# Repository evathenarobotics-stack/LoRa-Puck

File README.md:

So this week was a free design, But I was a little busy so I decided to follow the guide of the LoRa Puck.(though I wished I did the keyboard)
So I just followed the guide for the most part, But I did have some issues finding the symbols in the schematic.
When that issue occured, I just created my own by following a guide online and it seems to have worked quite well.

The main purpose of the lora (LOng RAnge) puck is to wirelessly communicate information through radio waves. This is why the schematic has the AE1 Antenna.
Without the use of wifi, celluar, and bluetooth, the lora puck is able to transfer information, such as temperature, motion, and more.
It uses a long lasting battery which makes it more reliable in situations where wifi isn't avaliable.

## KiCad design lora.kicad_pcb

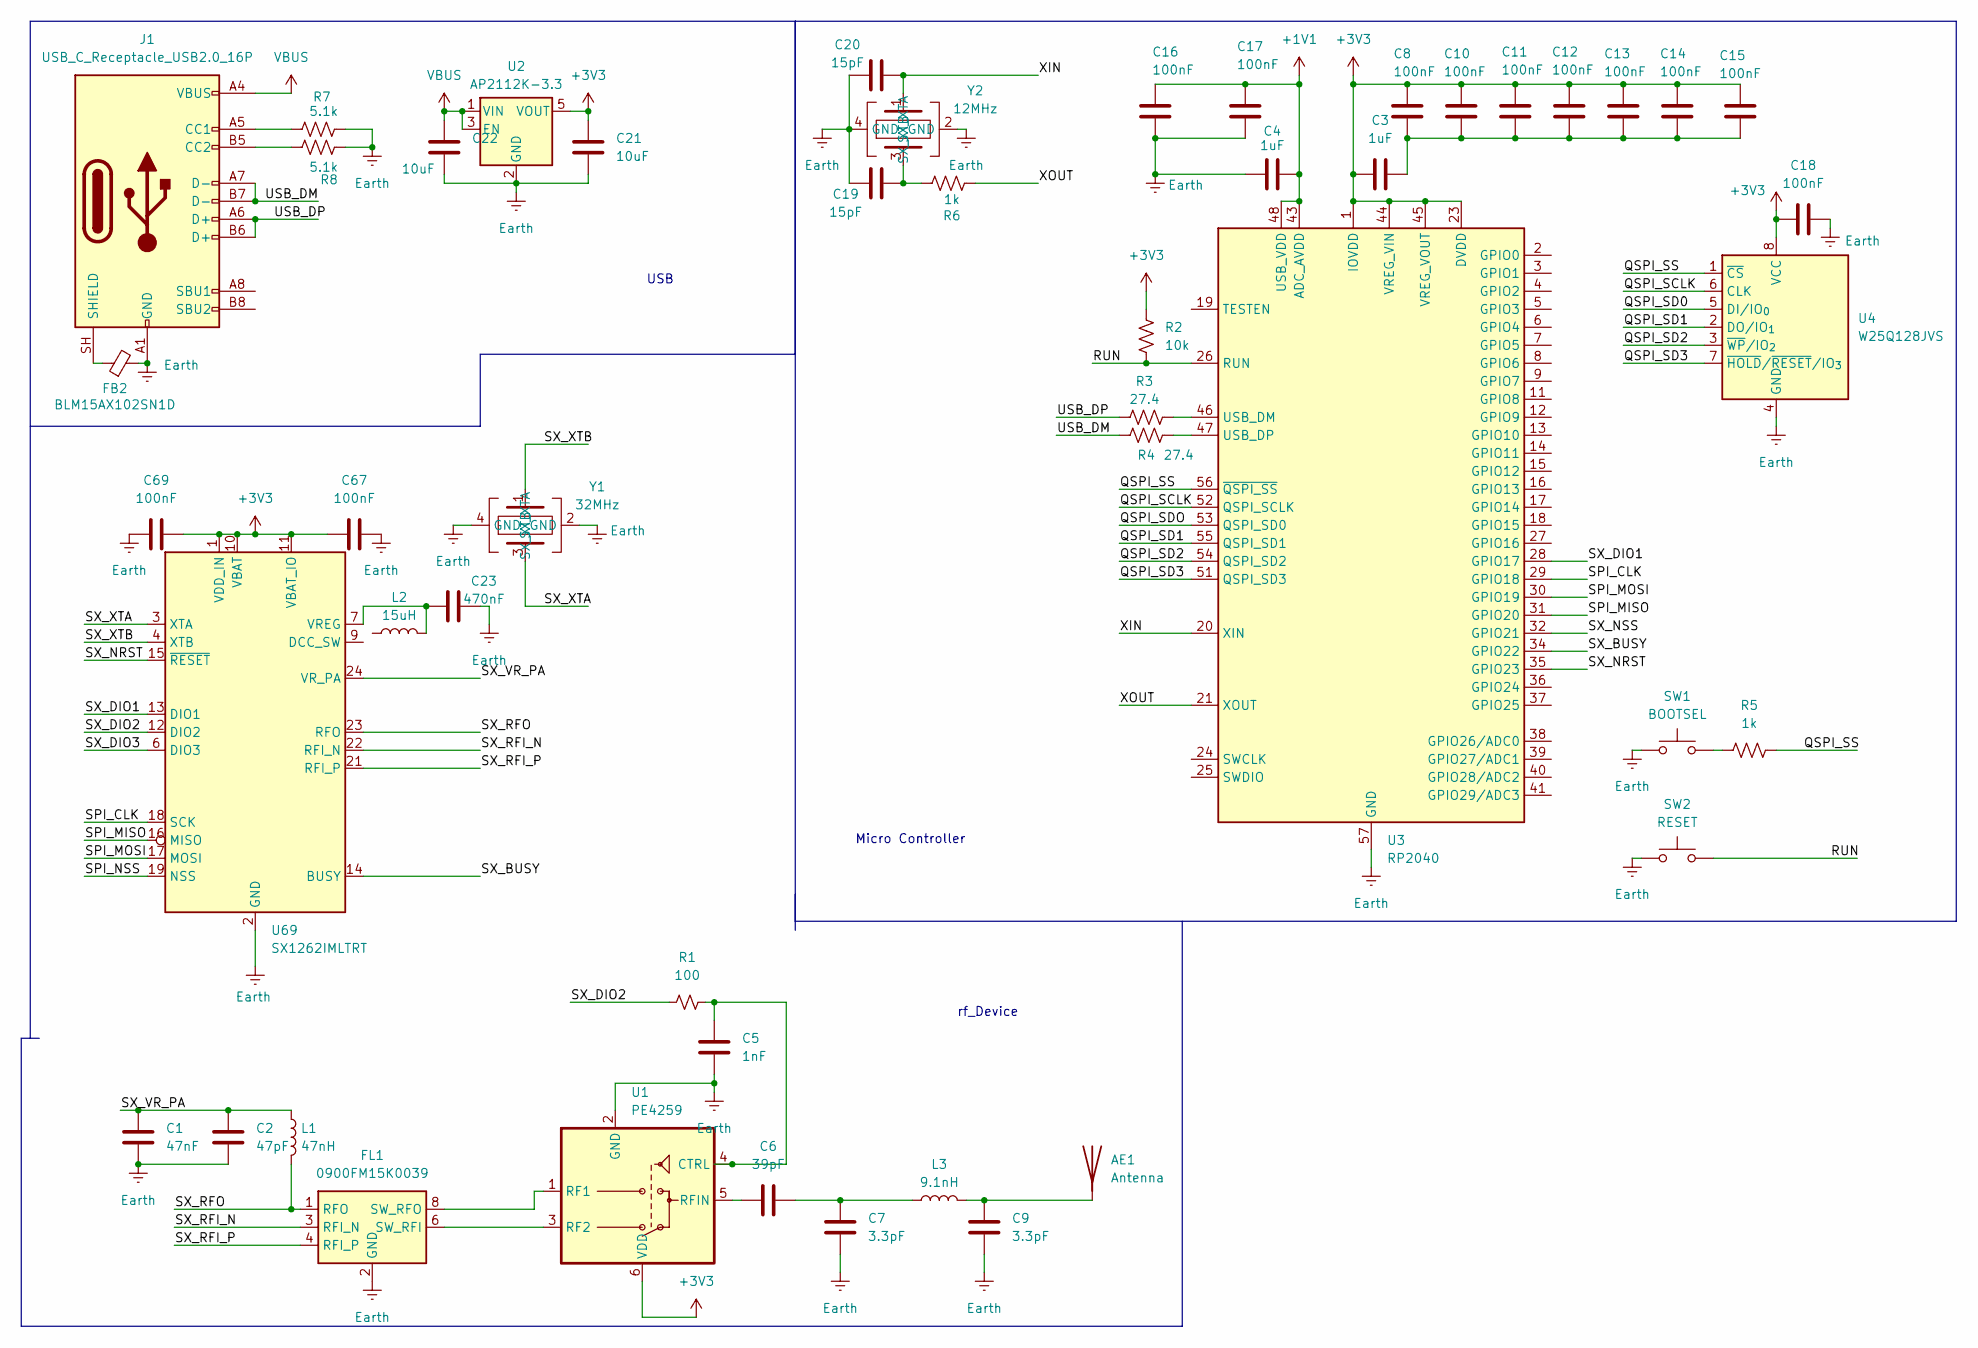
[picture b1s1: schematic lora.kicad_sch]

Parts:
AE1: Antenna; PinSocket_1x01_P2.54mm_Vertical
C1: 47nF; C_0402_1005Metric
C2: 47pF; C_0402_1005Metric
C3, C4: 1uF; C_0402_1005Metric
C5: 1nF; C_0402_1005Metric
C6: 39pF; C_0402_1005Metric
C7, C9: 3.3pF; C_0402_1005Metric
C8, C10, C11, C12, C13, C14, C15, C16, C17, C18, C67, C69: 100nF; C_0402_1005Metric
C19, C20: 15pF; C_0402_1005Metric
C21, C22: 10uF; C_0402_1005Metric
C23: 470nF; C_0402_1005Metric
FB2: BLM15AX102SN1D; L_0402_1005Metric
FL1: 0900FM15K0039; Balun_Johanson_0900FM15K0039
J1: USB_C_Receptacle_USB2.0_16P; USB_C_Receptacle_GCT_USB4105-xx-A_16P_TopMnt_Horizontal
L1: 47nH; L_0402_1005Metric
L2: 15uH; L_0402_1005Metric
L3: 9.1nH; L_0402_1005Metric
R1: 100; R_0603_1608Metric
R2: 10k; R_0603_1608Metric
R3, R4: 27.4; R_0603_1608Metric
R5, R6: 1k; R_0603_1608Metric
R7, R8: 5.1k; R_0603_1608Metric
SW1: BOOTSEL; SW_Tactile_SPST_NO_Straight_CK_PTS636Sx25SMTRLFS
SW2: RESET; SW_Tactile_SPST_NO_Straight_CK_PTS636Sx25SMTRLFS
U1: PE4259; SOT-363_SC-70-6
U2: AP2112K-3.3; SOT-23-5
U3: RP2040; QFN-56-1EP_7x7mm_P0.4mm_EP3.2x3.2mm
U4: W25Q128JVS; SOIC-8_5.3x5.3mm_P1.27mm
U69: SX1262IMLTRT; QFN-24-1EP_4x4mm_P0.5mm_EP2.6x2.6mm
Y1: 32MHz; Crystal_SMD_3225-4Pin_3.2x2.5mm
Y2: 12MHz; Crystal_SMD_SeikoEpson_TSX3225-4Pin_3.2x2.5mm

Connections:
+1V1: C4.2, C16.1, C17.1, U3.43 (ADC_AVDD), U3.48 (USB_VDD)
+3V3: C3.1, C8.1, C10.1, C11.1, C12.1, C13.1, C14.1, C15.1, C18.1, C21.1, C67.1, C69.2, R2.1, U1.6 (VDD), U2.5 (VOUT), U3.1 (IOVDD), U3.10 (IOVDD), U3.22 (IOVDD), U3.23 (DVDD), U3.33 (IOVDD), U3.42 (IOVDD), U3.44 (VREG_VIN), U3.45 (VREG_VOUT), U3.49 (IOVDD), U3.50 (DVDD), U4.8 (VCC), U69.1 (VDD_IN), U69.10 (VBAT), U69.11 (VBAT_IO)
/QSPI_SCLK: U3.52 (QSPI_SCLK), U4.6 (CLK)
/QSPI_SD0: U4.5 (DI/IO_{0})
/QSPI_SD1: U3.55 (QSPI_SD1), U4.2 (DO/IO_{1})
/QSPI_SD2: U3.54 (QSPI_SD2), U4.3 (~WP/IO_{2})
/QSPI_SD3: U3.51 (QSPI_SD3), U4.7 (~HOLD/~RESET/IO_{3})
/QSPI_SDO: U3.53 (QSPI_SD0)
/QSPI_SS: R5.1, U3.56 (~QSPI_SS), U4.1 (~CS)
/RUN: R2.2, SW2.2, U3.26 (RUN)
/SPI_CLK: U3.29 (GPIO18), U69.18 (SCK)
/SPI_MISO: U3.31 (GPIO20), U69.16 (MISO)
/SPI_MOSI: U3.30 (GPIO19), U69.17 (MOSI)
/SPI_NSS: U69.19 (NSS)
/SX_BUSY: U3.34 (GPIO22), U69.14 (BUSY)
/SX_DIO1: U3.28 (GPIO17), U69.13 (DIO1)
/SX_DIO2: R1.1, U69.12 (DIO2)
/SX_DIO3: U69.6 (DIO3)
/SX_NRST: U3.35 (GPIO23), U69.15 (~RESET)
/SX_NSS: U3.32 (GPIO21)
/SX_RFI_N: FL1.3 (RFI_N), U69.22 (RFI_N)
/SX_RFI_P: FL1.4 (RFI_P), U69.21 (RFI_P)
/SX_RFO: FL1.1 (RFO), L1.2, U69.23 (RFO)
/SX_VR_PA: C1.1, C2.1, L1.1, U69.24 (VR_PA)
/SX_XTA: U69.3 (XTA), Y1.3 (SX_XTA)
/SX_XTB: U69.4 (XTB), Y1.1 (SX_XTB)
/USB_DM: J1.A7 (D-), J1.B7 (D-), R4.1
/USB_DP: J1.A6 (D+), J1.B6 (D+), R3.1
/XIN: C20.2, U3.20 (XIN), Y2.1 (SX_XTB)
/XOUT: R6.2, U3.21 (XOUT)
Earth: C1.2, C2.2, C4.1, C5.2, C7.1, C9.2, C16.2, C17.2, C18.2, C19.1, C20.1, C21.2, C22.2, C23.2, C67.2, C69.1, FB2.2, FL1.2 (GND), FL1.5 (GND), FL1.7 (GND), FL1.9 (GND), FL1.10 (GND), J1.A1 (GND), J1.A12 (GND), J1.B1 (GND), J1.B12 (GND), R7.2, R8.2, SW1.1, SW2.1, U1.2 (GND), U2.2 (GND), U3.57 (GND), U4.4 (GND), U69.2 (GND), U69.5 (GND), U69.8 (GND), U69.20 (GND), U69.25 (GND), Y1.2 (GND), Y1.4 (GND), Y2.2 (GND), Y2.4 (GND)
unnamed: AE1.1 (A_1), C9.1, L3.2
unnamed: C6.2, C7.2, L3.1
unnamed: C3.2, C8.2, C10.2, C11.2, C12.2, C13.2, C14.2, C15.2
unnamed: FL1.6 (SW_RFI), U1.3 (RF2)
unnamed: FL1.8 (SW_RFO), U1.1 (RF1)
unnamed: J1.A5 (CC1), R7.1
unnamed: J1.B5 (CC2), R8.1
unnamed: FB2.1, J1.SH (SHIELD)
unnamed: R5.2, SW1.2
unnamed: C5.1, R1.2, U1.4 (CTRL)
unnamed: C6.1, U1.5 (RFIN)
unnamed: R3.2, U3.46 (USB_DM)
unnamed: R4.2, U3.47 (USB_DP)
unnamed: C23.1, L2.2 (2_2), U69.7 (VREG)
unnamed: C19.2, R6.1, Y2.3 (SX_XTA)
VBUS: C22.1, J1.A4 (VBUS), J1.A9 (VBUS), J1.B4 (VBUS), J1.B9 (VBUS), U2.1 (VIN), U2.3 (EN)

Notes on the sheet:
Micro Controller
USB
rf_Device

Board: 4 copper layers, 49 parts (0 on the bottom side), 42 nets, no tracks yet.
